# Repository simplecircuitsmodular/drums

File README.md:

# Drums

## Features
These modules features 6 individually triggered and tuned drum voices in one module. The code was written Jan Ostman. I have chosen to rehost the code here for other's convenience as Jan's hosting method introduced numerous endlines that prevented the code from compiling. Jan's source code can be found here:

[Western Drums, DSP-D8](https://janostman.wordpress.com/2016/01/03/the-dsp-d8-drumchip-source-code/)

[Latin Drums, DSP-L8](https://janostman.wordpress.com/2016/01/04/the-dsp-l8-latin-perc-source-code/)

## Files
### westernDrums_01.ino and latinDrums_01.ino
This is the Arduino code. An ISP header on the board allows the microcontroller to be programmed directly. The code was written by Jan Ostman. The Features section has links to Jan's source code.

### drums_xx.brd and .sch
These are the Eagle files for the PCB. To order PCBs, gerbers need to be generated using a CAM job in Eagle. A free version of Eagle is available that can do this. Both the latin and western drums use the same board, the only difference is the panel and code.

### drumsParts_xx.md
This is the parts list. A Mouser BOM is available at in this file as well.

### westernDrums.ai and latinDrums.ai
This is the panel in Adobe Illustrator format. This can be used to manufacture a panel, which I do with 1/8" acrylic and a laser cutter.

## Updates

### 01.1 30JUL18

Verified design. All functions work, though two issues were found. Added values to Eagle files for resistors and capacitors. Updated .brd to fix ISP issue, though this is currently untested. All signals were rerouted.

### 01 24JUN18
First push to GitHub. Currently this design is untested.

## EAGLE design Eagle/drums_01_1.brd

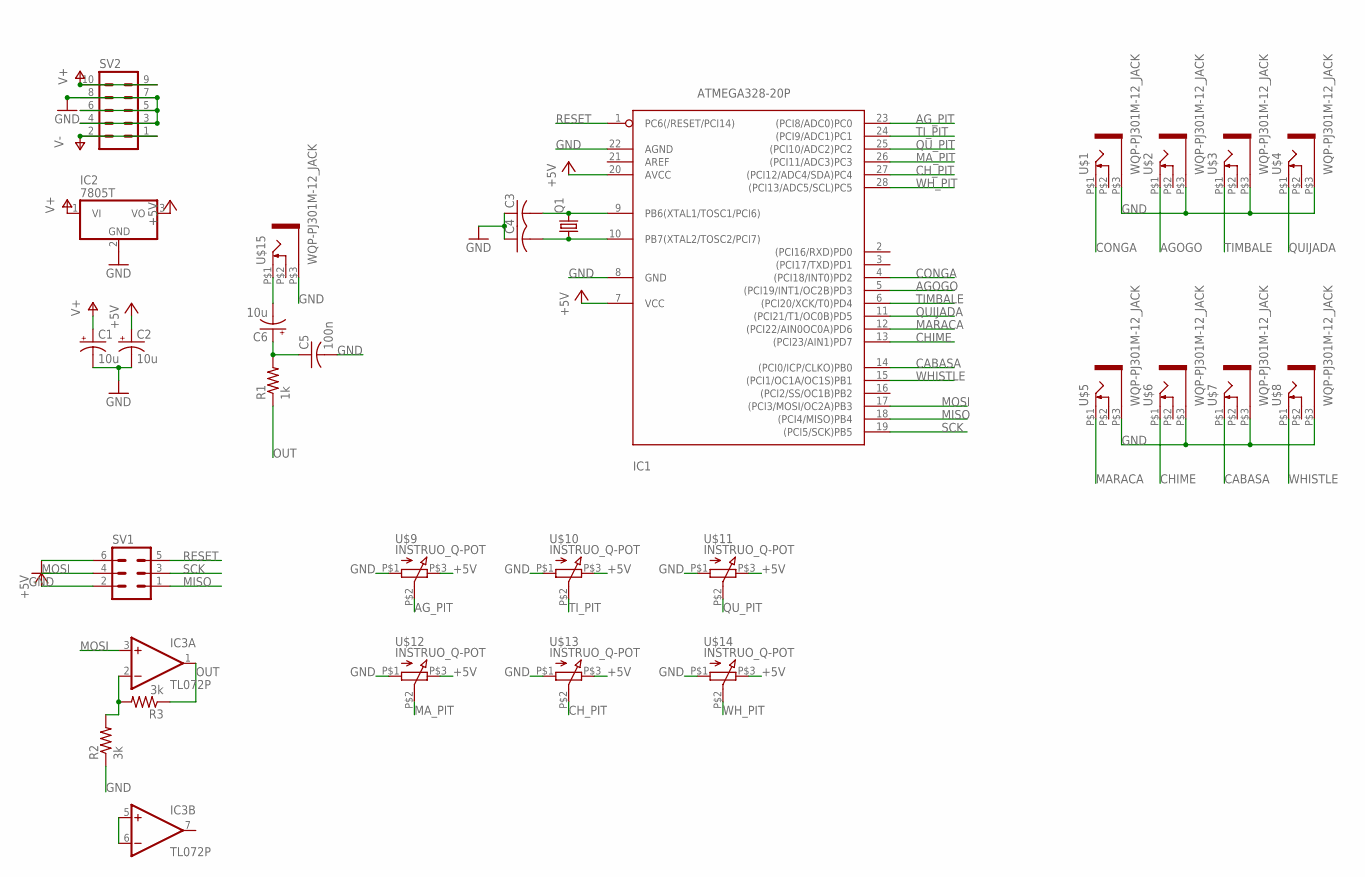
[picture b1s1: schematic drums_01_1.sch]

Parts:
C1, C2, C6: 10u; E2,5-6
C3, C4: C-US025-024X044; C025-024X044
C5: 100n; C025-024X044
IC1: ATMEGA328-20P; DIL28-3
IC2: 7805T; TO220H
IC3: TL072P; DIL08
Q1: CRYSTALHC49U-V; HC49U-V
R1: 1k; 0207/12
R2, R3: 3k; 0207/12
SV1: MA03-2
SV2: MA05-2
U$1, U$2, U$3, U$4, U$5, U$6, U$7, U$8, U$15: WQP-PJ301M-12_JACK
U$9, U$10, U$11, U$12, U$13, U$14: INSTRUO_Q-POT

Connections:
+5V: C2.+, IC1.7 (VCC), IC1.20 (AVCC), IC2.3 (VO), SV1.2, U$9.P$3 (3), U$10.P$3 (3), U$11.P$3 (3), U$12.P$3 (3), U$13.P$3 (3), U$14.P$3 (3)
AGOGO: IC1.5 ((PCI19/INT1/OC2B)PD3), U$2.P$1 (2)
AG_PIT: IC1.23 ((PCI8/ADC0)PC0), U$9.P$2 (2)
CABASA: IC1.14 ((PCI0/ICP/CLKO)PB0), U$7.P$1 (2)
CHIME: IC1.13 ((PCI23/AIN1)PD7), U$6.P$1 (2)
CH_PIT: IC1.27 ((PCI12/ADC4/SDA)PC4), U$13.P$2 (2)
CONGA: IC1.4 ((PCI18/INT0)PD2), U$1.P$1 (2)
GND: C1.-, C2.-, C3.1, C4.1, C5.2, IC1.8 (GND), IC1.22 (AGND), IC2.2 (GND), R2.1, SV1.6, SV2.3, SV2.4, SV2.5, SV2.6, SV2.7, SV2.8, U$1.P$3 (1), U$2.P$3 (1), U$3.P$3 (1), U$4.P$3 (1), U$5.P$3 (1), U$6.P$3 (1), U$7.P$3 (1), U$8.P$3 (1), U$9.P$1 (1), U$10.P$1 (1), U$11.P$1 (1), U$12.P$1 (1), U$13.P$1 (1), U$14.P$1 (1), U$15.P$3 (1)
MARACA: IC1.12 ((PCI22/AIN0OC0A)PD6), U$5.P$1 (2)
MA_PIT: IC1.26 ((PCI11/ADC3)PC3), U$12.P$2 (2)
MISO: IC1.18 ((PCI4/MISO)PB4), SV1.1
MOSI: IC1.17 ((PCI3/MOSI/OC2A)PB3), IC3.3 (+IN), SV1.4
unnamed: C3.2, IC1.9 (PB6(XTAL1/TOSC1/PCI6)), Q1.2
unnamed: C4.2, IC1.10 (PB7(XTAL2/TOSC2/PCI7)), Q1.1
unnamed: C6.-, U$15.P$1 (2)
unnamed: C5.1, C6.+, R1.2
unnamed: IC3.5 (+IN), IC3.6 (-IN)
unnamed: IC3.2 (-IN), R2.2, R3.2
OUT: IC3.1 (OUT), R1.1, R3.1
QUIJADA: IC1.11 ((PCI21/T1/OC0B)PD5), U$4.P$1 (2)
QU_PIT: IC1.25 ((PCI10/ADC2)PC2), U$11.P$2 (2)
RESET: IC1.1 (PC6(/RESET/PCI14)), SV1.5
SCK: IC1.19 ((PCI5/SCK)PB5), SV1.3
TIMBALE: IC1.6 ((PCI20/XCK/T0)PD4), U$3.P$1 (2)
TI_PIT: IC1.24 ((PCI9/ADC1)PC1), U$10.P$2 (2)
V+: C1.+, IC2.1 (VI), IC3.8 (V+), SV2.9, SV2.10
V-: IC3.4 (V-), SV2.1, SV2.2
WHISTLE: IC1.15 ((PCI1/OC1A/OC1S)PB1), U$8.P$1 (2)
WH_PIT: IC1.28 ((PCI13/ADC5/SCL)PC5), U$14.P$2 (2)

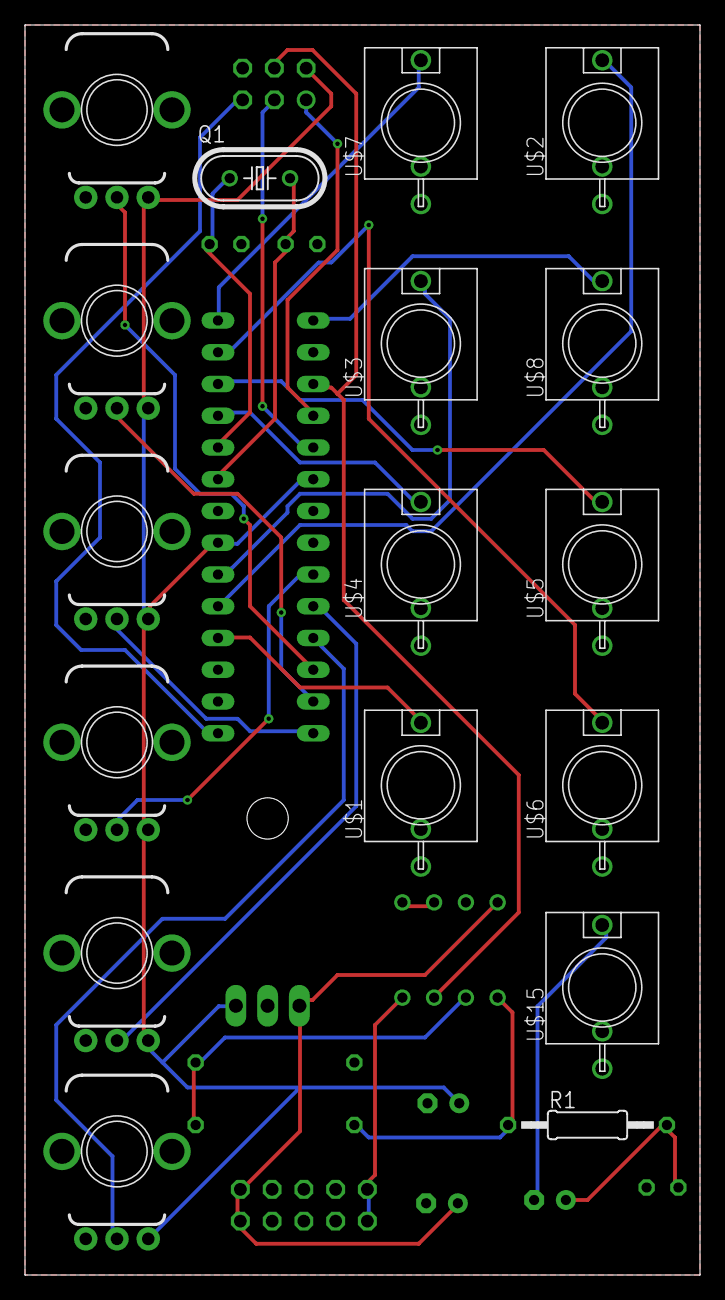
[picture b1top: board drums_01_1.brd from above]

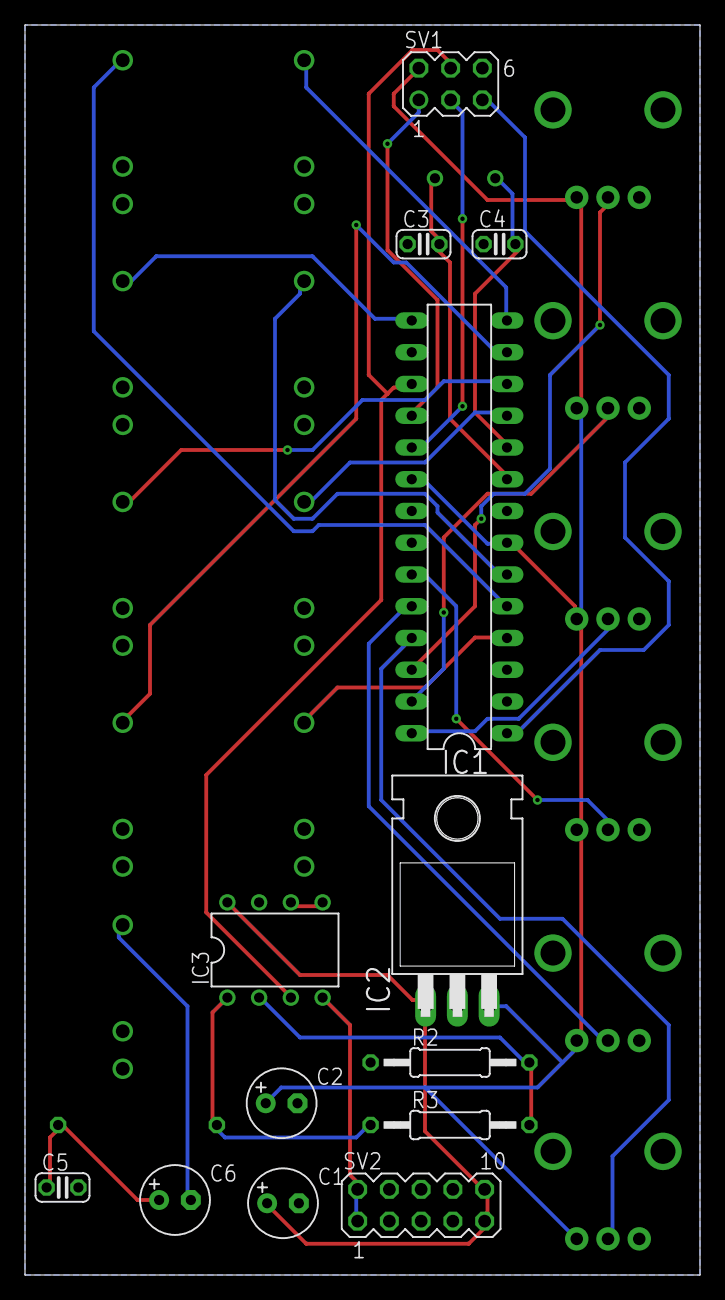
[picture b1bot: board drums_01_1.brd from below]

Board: 2 copper layers, 54.0 x 100.0 mm, 30 parts (13 on the bottom side), 29 nets.

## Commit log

2018-07-26 Add site
2018-07-26 Set theme jekyll-theme-minimal
2018-07-26 update site
2018-07-31 Fix ISP issue. Update README.
2018-07-31 Fix file names
2018-07-31 Add License
2018-07-31 Update parts
2018-08-22 Add Panel
2018-12-03 Site Update
2018-12-25 ReadMe Changes
2018-12-25 Add photo
2019-08-28 Website Updates
